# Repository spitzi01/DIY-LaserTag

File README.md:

# ESP32-LaserTag
Easy Open Source LaserTag System
### Überblick
Ziel dieses Projektes war der Bau eines einfachen LaserTag-Systems. Es sollte schnell und mit wenig Hardware an beliebigen Orten aufbaubar sein und  und über ein Handy gesteuert werden können.

Weitere Features sind:

- Soundausgabe für Schuss, Treffer und Nachladen (insgesamt 5 Verschiedene)
- Display in jedem Tagger
- lange Akkulaufzeit des gesamten Systems
- 3 Spielmodi
- Taschenlampe
- rote Laserdiode für Schuss-Simulation
- 5 in den Tagger integriete Infrarot-Empfänger
    
Das LaserTag-System besteht aus zwei elementaren Bestandteilen. Die Basisstation dient als Verbindungsglied zwischen den Taggern, der einzelnen Spieler, und einer HTTP-Website, welche der Konfiguration und Auswertung dient. Der Datenaustausch mit den Spielern erfolgt drahtlos mit Hilfe des EspNow-Protokolls der ESP32 S2 Mikrocontroller. Zum Spielen sind zwischen 2 und 10 Tagger notwendig. Für den Capture the Flag Spielmodus werden zusätzlich noch Flags benötigt, die die Basis und Spawnpunkt eines Team markieren.

### Basisstation

Nach dem Einschalten der Basisstation wird ein WLAN-Netzwerk erzeugt und die Konfigurationswebsite gehostet. Wenn man sich hier mit einem Smartphone einloggt, kann man die Anzahl der Spieler, Dauer des Spiels, Modus, Namen der Spieler und Teamzugehörigkeit einstellen. Die maximal 10 Spieler können auf 6 Teams verteilt werden. Vor dem Starten des Spiels mit dem Start-Taster müssen unbedingt alle Tagger, die verwendet werden sollen, eingeschaltet werden, damit diese von der Basisstation ihre Informationen erhalten können. Nach Ablauf der Spieldauer übermitteln die Tagger automatisch die Spielstände an die Basisstation und schalten sich ab. Die Basisstation berechnet die Ergebnisse und hostet diese in Form einer Website. Das hat den Vorteil, dass sich theoretisch mehrere Spieler die Ergebnisse auf ihren Smartphones anschauen können.

### Tagger

Bei einem Testsystem wurde festgestellt, dass es dem Spieler nicht möglich sein darf, seinen Tagger aus Versehen auszuschalten. Deshalb wird die Schaltung durch einen Taster aktiviert und nur durch den Mikrocontroller wieder deaktiviert. Außerdem soll der Spieler immer beide Hände am Tagger haben. So soll verhindert werden, dass man mit einer Hand Sensoren abdecken könnte. Dies wird durch einen Taster in Reihe zum eigentlichen Abzug realisiert. Gleichzeitig schaltet dieser auch die Taschenlampe an. In meinem Fall dient ein kleiner 12V Bleiakku aus einer Brandmeldezentrale als Energieversorgung. Mit Hilfe des Step Down Converters wird eine hohe Effizienz und Akkulaufzeit erreicht. Das Display hat 20 alphanumerische Stellen, welche die Namen der Spieler und die Anzahl der Leben anzeigen. Eine Hintergrundbeleuchtung ist nicht vorhanden, da diese zu viel Strom benötigen würde. Deshalb dient die RGB-LED für die Teamzugehörigkeit als Beleuchtung. Edit: Mittlerweile wurde das Display durch ein OLED 0,96" Display getauscht, da das LCD Display nicht mehr verfügbar war. Ebenso wurde der Akku durch einen günstigen 12V Lithium-Ionen Akku ersetzt.

Der Schuss wird durch eine Laserdiode visualisiert. Die eigentliche Information findet durch eine IR-Übertragung ihren Weg zu anderen Spielern. Bei Tests in der Nacht konnte eine Reichweite von bis zu 60 Meter erzielt werden. Der kurze Alu-Lauf dient als Reflektor für die Infrarot-LED und auch als Kühlkörper, da bei aktiviertem Schnellfeuermodus die LED sehr belastet wird.

Die verfügbaren Spielmodi sind:

- Standard (Spielen in Teams oder Einzeln, Reaktivierung nach ca. 20 Sekunden)
- Battle Royal (Spielen in Teams oder Einzeln, Leben werden bei Treffer weniger, kein Treffer in gewisser Zeit fügt ein Leben hinzu, lange Reaktivierungszeit ca. 2 Minuten)
- Capture the Flag (2 Teams rot & blau, Flags markieren Basis oder Spawnpunkt des jeweiligen Teams, Reaktivierung nur im Bereich des eigenen Spawnpunkts, Punkte bei Aufenthalt in gegnerischen Basis)

### Flag
Ein Flag sendet in regelmäßigen Abständen einen Code der von den Taggern empfangen wird. Bereich, in dem das Signal empfangbar ist, beträgt in etwa 5-8 Meter im Radius. Diese Strecke ergibt sich durch den Einsatz von ESP32 S2 Mikrocontroller ohne integriete Antenne in den Taggern.

### Verbesserungsmöglichkeiten

- Reichweite bei starkem Sonnenschein eingeschränkt
- Mikrocontroller überträgt kurzes Störgeräusch über I2S nach Ende einer Soundausgabe (Software Problem)
- Skalierbarkeit (mehr als 10 Spieler)

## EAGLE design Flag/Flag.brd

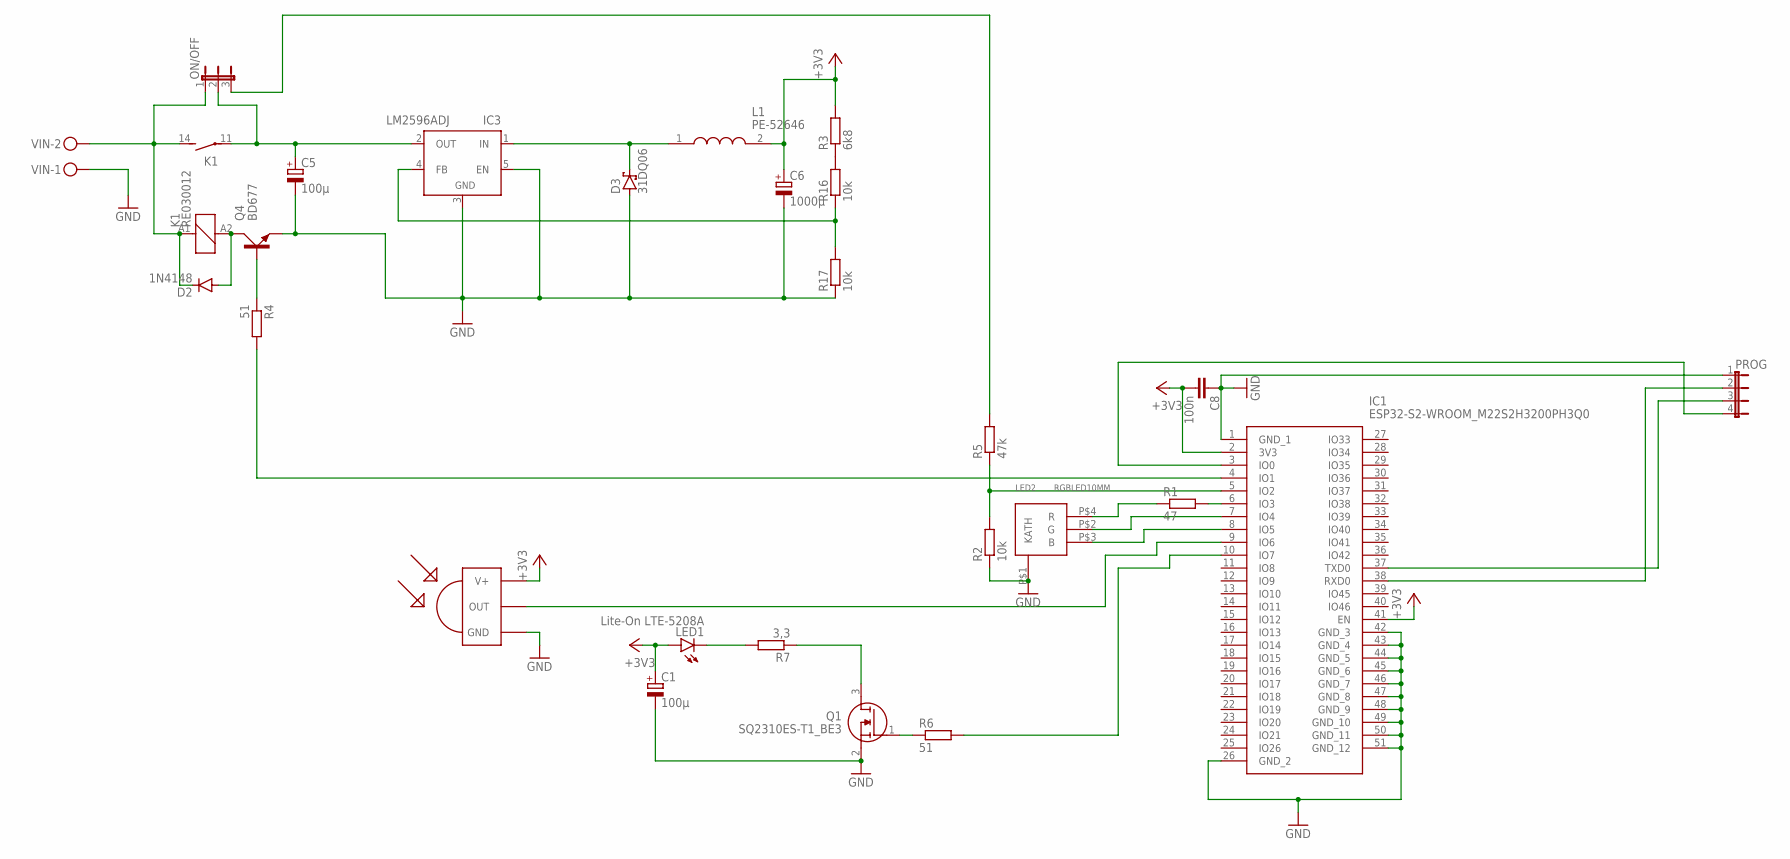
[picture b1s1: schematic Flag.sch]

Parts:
C1: 100µ; E3,5-8
C5: 100µ; E5-10,5
C6: 1000µ; E3,5-8
C8: 100n; C050-025X075
D2: 1N4148; SOD80C
D3: 31DQ06; C4111-15
IC1: ESP32-S2-WROOM_M22S2H3200PH3Q0; ESP32S2WROOMM22S2H3200PH3Q0
IC3: LM2596ADJ; TO220-52
K1: RE030012; RE-SCHRACK
L1: PE-52646; PE52646
LED1: Lite-On LTE-5208A; LED5MM
LED2: RGBLED10MM
ON/OFF: JP2E; JP2
PROG: JP4E; JP4
Q1: SQ2310ES-T1_BE3; SOT95P237X112-3N
Q4: BD677; TO126AV
R1: 47; 0207/10
R2: 10k; 0207/10
R3: 6k8; R1206
R4, R6: 51; R1206
R5: 47k; 0207/10
R7: 3,3; 0207/10
R16, R17: 10k; R1206
U1: TSOP33338; TSOP18XX
VIN: MKDSN1,5/2-5,08

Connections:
+3V3: C1.+, C6.+, C8.2, IC1.2 (3V3), IC1.41 (EN), L1.2, LED1.A, R3.2, U1.VCC (V+)
GND: C1.-, C5.-, C6.-, C8.1, D3.A, IC1.1 (GND_1), IC1.26 (GND_2), IC1.42 (GND_3), IC1.43 (GND_4), IC1.44 (GND_5), IC1.45 (GND_6), IC1.46 (GND_7), IC1.47 (GND_8), IC1.48 (GND_9), IC1.49 (GND_10), IC1.50 (GND_11), IC1.51 (GND_12), IC3.3 (GND), IC3.5 (EN), LED2.P$1 (KATH), PROG.1, Q1.2 (S), Q4.E, R2.1, R17.1, U1.GND, VIN.1
unnamed: C5.+, IC3.2 (OUT), K1.11, ON/OFF.2
unnamed: IC1.4 (IO1), R4.2
unnamed: D2.C, K1.14 (S), K1.A1 (1), ON/OFF.1, VIN.2
unnamed: D2.A, K1.A2 (2), Q4.C
unnamed: LED2.P$4 (R), R1.1
unnamed: IC1.7 (IO4), LED2.P$2 (G)
unnamed: IC1.8 (IO5), LED2.P$3 (B)
unnamed: D3.C, IC3.1 (IN), L1.1
unnamed: IC3.4 (FB), R16.1, R17.2
unnamed: IC1.6 (IO3), R1.2
unnamed: IC1.5 (IO2), R2.2, R5.1
unnamed: IC1.9 (IO6), U1.OUT
unnamed: ON/OFF.3, R5.2
unnamed: IC1.10 (IO7), R6.2
unnamed: Q1.1 (G), R6.1
unnamed: LED1.K (C), R7.2
unnamed: Q1.3 (D), R7.1
unnamed: Q4.B, R4.1
unnamed: IC1.3 (IO0), PROG.4
unnamed: IC1.37 (TXD0), PROG.3
unnamed: IC1.38 (RXD0), PROG.2
unnamed: R3.1, R16.2

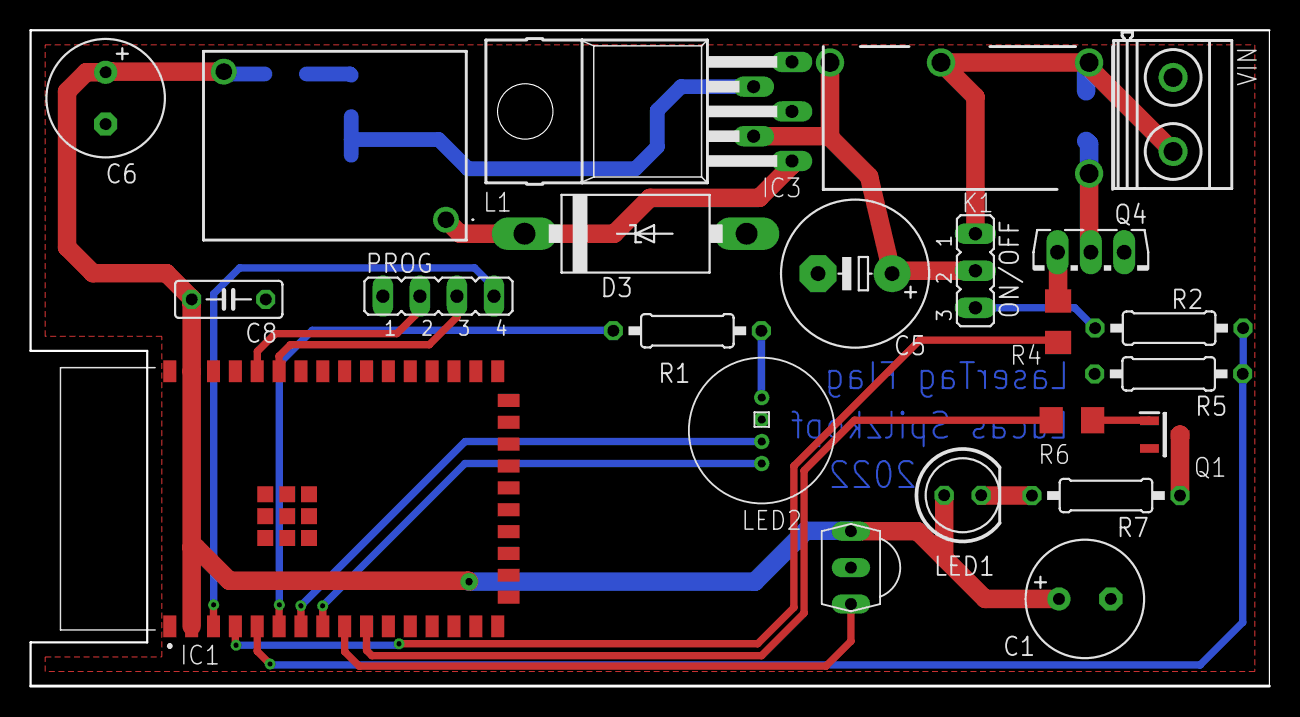
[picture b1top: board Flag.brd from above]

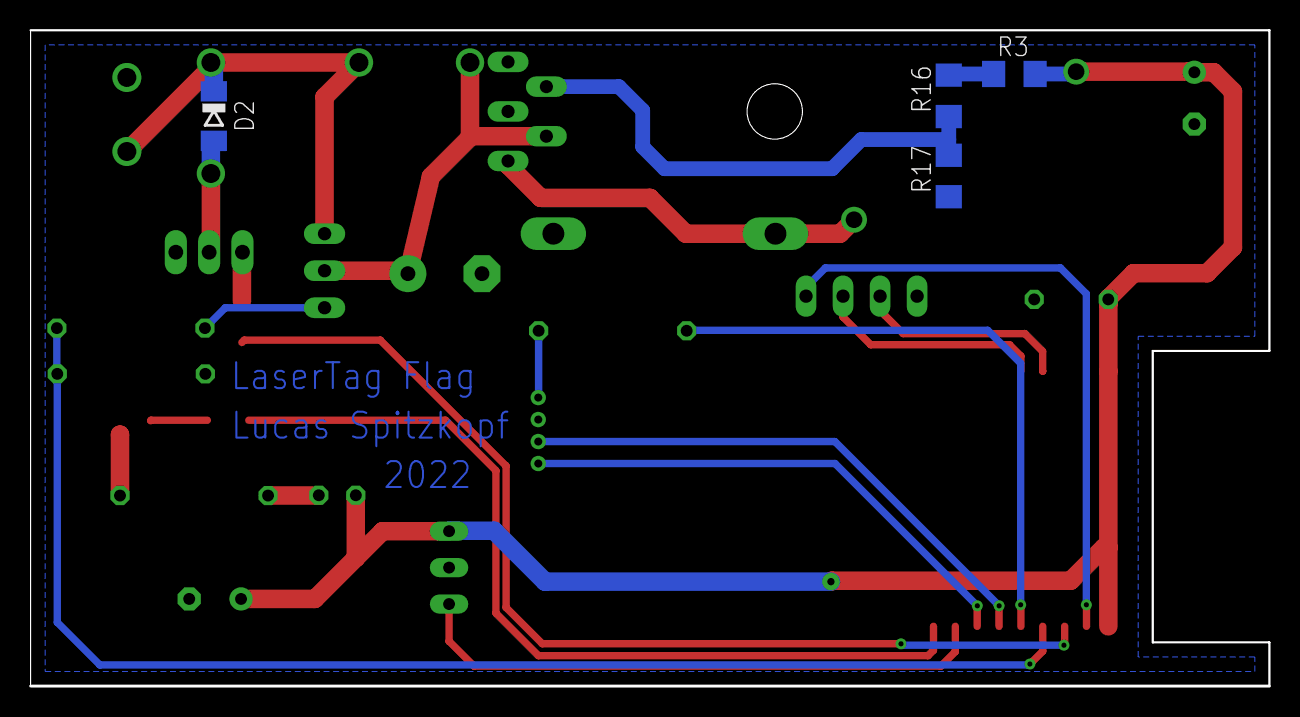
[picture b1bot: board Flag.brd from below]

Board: 2 copper layers, 85.0 x 45.0 mm, 27 parts (4 on the bottom side), 24 nets.

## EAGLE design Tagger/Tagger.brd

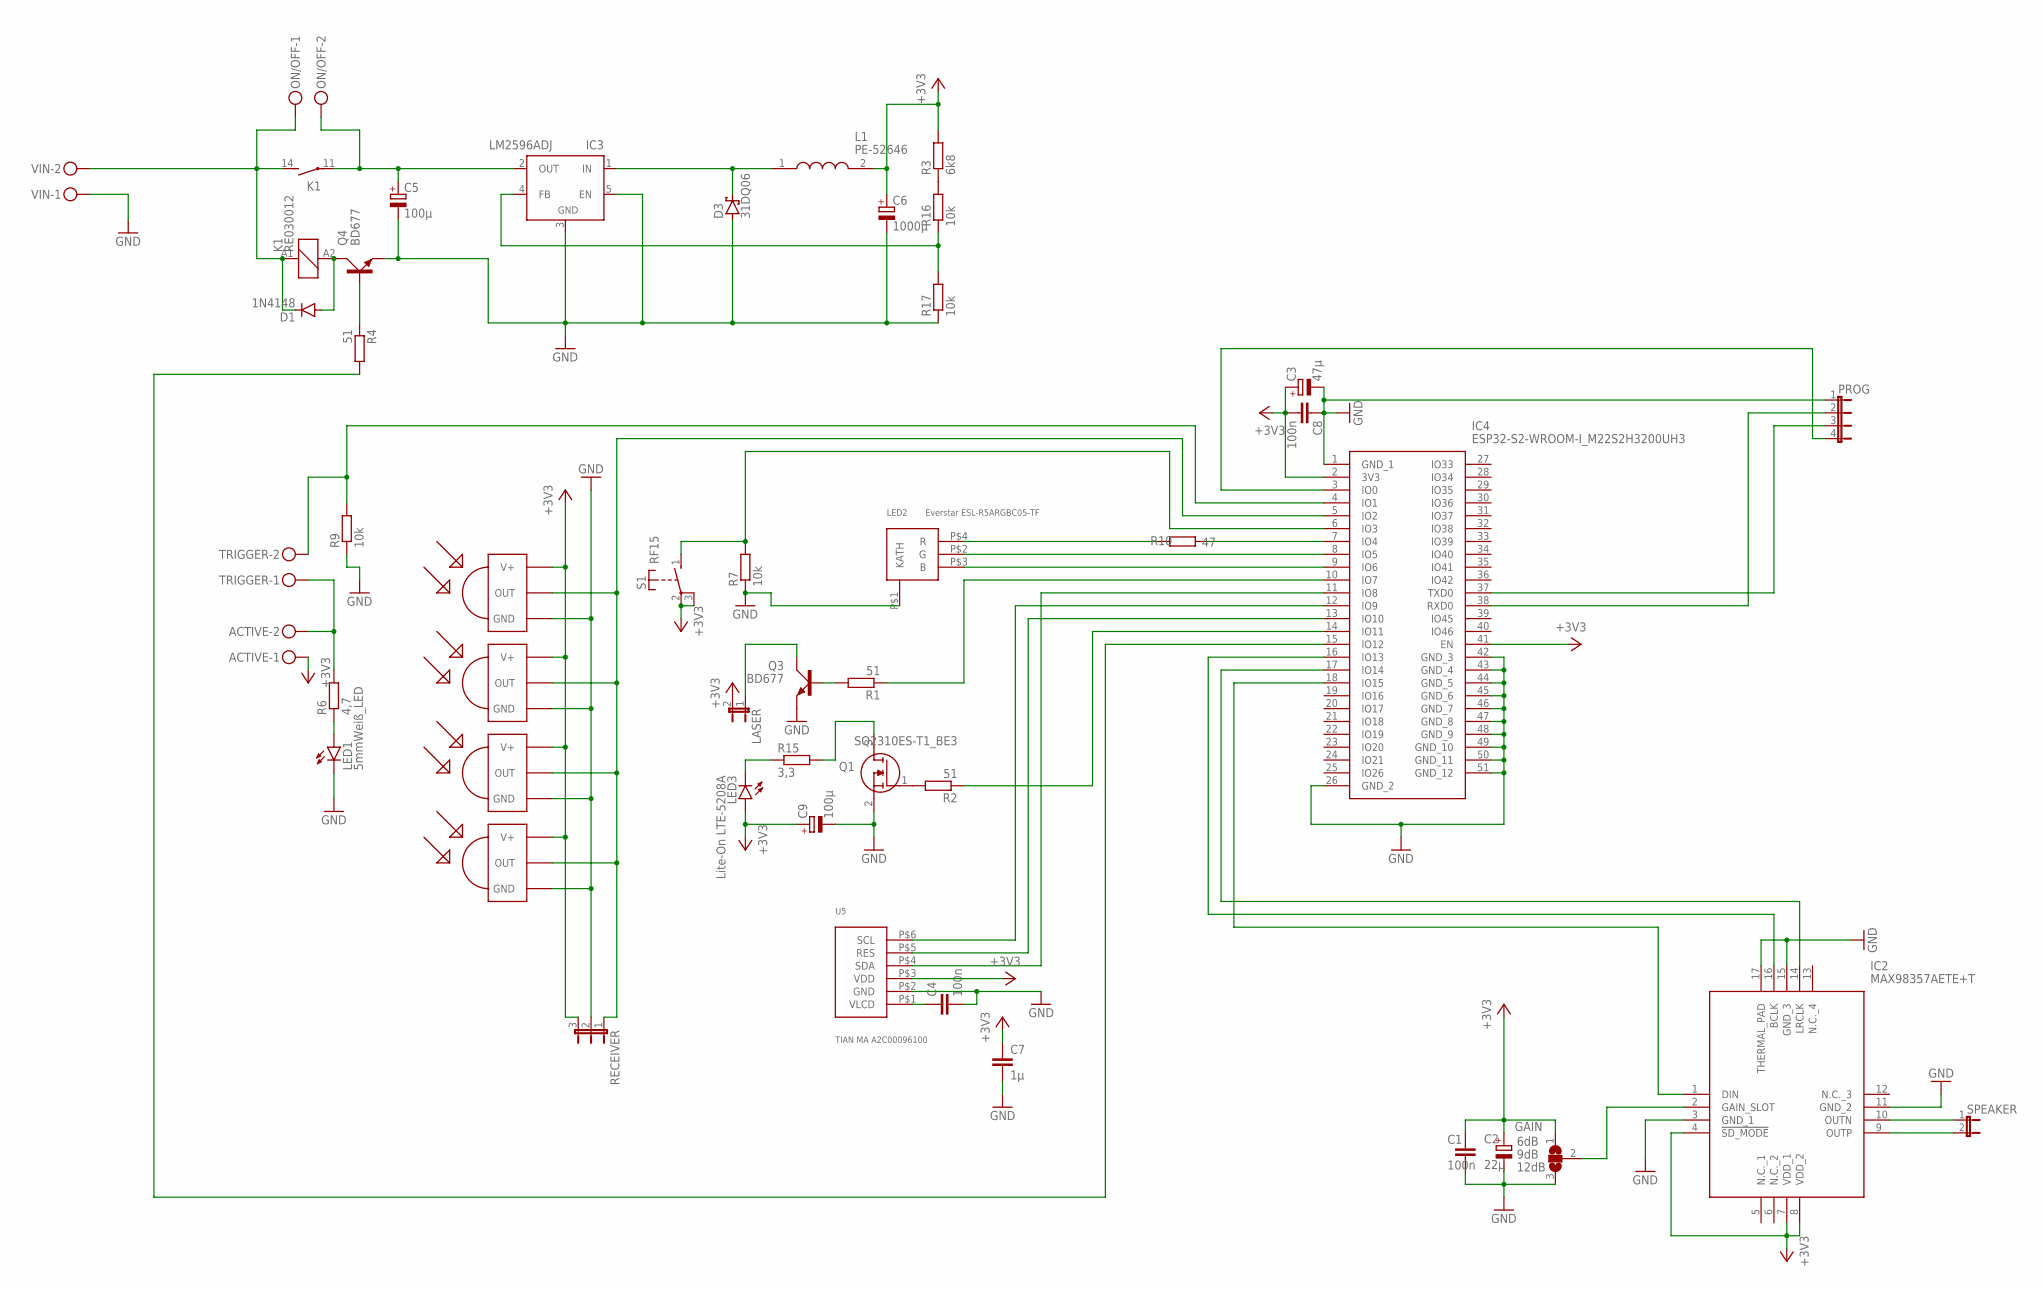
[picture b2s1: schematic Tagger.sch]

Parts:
ACTIVE: MKDSN1,5/2-5,08
C1, C4, C8: 100n; C1206
C2: 22µ; E2-5
C3: 47µ; E2-5
C5: 100µ; E2,5-6E
C6: 1000µ; E5-10,5
C7: 1µ; C0805
C9: 100µ; E2,5-6
D1: 1N4148; SOD80C
D3: 31DQ06; C4111-15
GAIN: SJ2WW; SJ_2W
IC2: MAX98357AETE+T; QFN50P300X300X80-17N
IC3: LM2596ADJ; TO220-52
IC4: ESP32-S2-WROOM-I_M22S2H3200UH3; ESP32S2WROOMIM22S2H3200UH3Q0
K1: RE030012; RE-SCHRACK
L1: PE-52646; PE52646
LASER: JP1E; JP1
LED1: 5mmWeiß_LED; LED5MM
LED2: Everstar ESL-R5ARGBC05-TF; RGBLED5MM
LED3: Lite-On LTE-5208A; LED5MM
ON/OFF: MKDSN1,5/2-5,08
PROG: JP4E; JP4
Q1: SQ2310ES-T1_BE3; SOT95P237X112-3N
Q3, Q4: BD677; TO126AV
R1, R2, R4: 51; R1206
R3: 6k8; R1206
R6: 4,7; 0207/10
R7, R9, R16, R17: 10k; R1206
R10: 47; 0207/10
R15: 3,3; 0207/10
RECEIVER: JP2E; JP2
S1: RF15
SPEAKER: JP1E; JP1
TRIGGER: MKDSN1,5/2-5,08
U1, U2, U3, U4: TSOP33338; TSOP18XX
U5: TIAN MA A2C00096100; LCD_DISPLAY
VIN: MKDSN1,5/2-5,08

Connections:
+3V3: ACTIVE.1, C1.1, C2.+, C3.+, C6.+, C7.1, C8.2, C9.+, GAIN.1, IC2.4 (!SD_MODE), IC2.7 (VDD_1), IC2.8 (VDD_2), IC4.2 (3V3), IC4.41 (EN), L1.2, LASER.2, LED3.A, R3.2, RECEIVER.3, S1.2, S1.3, U1.VCC (V+), U2.VCC (V+), U3.VCC (V+), U4.VCC (V+), U5.P$3 (VDD)
GND: C1.2, C2.-, C3.-, C4.2, C5.-, C6.-, C7.2, C8.1, C9.-, D3.A, GAIN.3, IC2.3 (GND_1), IC2.11 (GND_2), IC2.15 (GND_3), IC2.17 (THERMAL_PAD), IC3.3 (GND), IC3.5 (EN), IC4.1 (GND_1), IC4.26 (GND_2), IC4.42 (GND_3), IC4.43 (GND_4), IC4.44 (GND_5), IC4.45 (GND_6), IC4.46 (GND_7), IC4.47 (GND_8), IC4.48 (GND_9), IC4.49 (GND_10), IC4.50 (GND_11), IC4.51 (GND_12), LED1.K (C), LED2.P$1 (KATH), PROG.1, Q1.2 (S), Q3.E, Q4.E, R7.1, R9.1, R17.1, RECEIVER.2, U1.GND, U2.GND, U3.GND, U4.GND, U5.P$2 (GND), VIN.1
unnamed: C5.+, IC3.2 (OUT), K1.11, ON/OFF.2
unnamed: GAIN.2, IC2.2 (GAIN_SLOT)
unnamed: D1.C, K1.14 (S), K1.A1 (1), ON/OFF.1, VIN.2
unnamed: D1.A, K1.A2 (2), Q4.C
unnamed: IC4.7 (IO4), R10.2
unnamed: IC2.10 (OUTN), SPEAKER.1
unnamed: IC2.1 (DIN), IC4.18 (IO15)
unnamed: C4.1, U5.P$1 (VLCD)
unnamed: D3.C, IC3.1 (IN), L1.1
unnamed: IC3.4 (FB), R16.1, R17.2
unnamed: IC2.14 (LRCLK), IC4.17 (IO14)
unnamed: IC4.14 (IO11), R2.1
unnamed: LED3.K (C), R15.1
unnamed: LASER.1, Q3.C
unnamed: LED1.A, R6.1
unnamed: IC4.11 (IO8), U5.P$4 (SDA)
unnamed: Q1.3 (D), R15.2
unnamed: IC4.6 (IO3), R7.2, S1.1 (S)
unnamed: Q4.B, R4.1
unnamed: LED2.P$4 (R), R10.1
unnamed: IC4.8 (IO5), LED2.P$2 (G)
unnamed: IC4.9 (IO6), LED2.P$3 (B)
unnamed: IC2.16 (BCLK), IC4.16 (IO13)
unnamed: IC4.4 (IO1), R9.2, TRIGGER.2
unnamed: IC4.10 (IO7), R1.1
unnamed: Q3.B, R1.2
unnamed: IC4.13 (IO10), U5.P$5 (RES)
unnamed: IC4.12 (IO9), U5.P$6 (SCL)
unnamed: IC2.9 (OUTP), SPEAKER.2
unnamed: IC4.3 (IO0), PROG.4
unnamed: Q1.1 (G), R2.2
unnamed: IC4.5 (IO2), RECEIVER.1, U1.OUT, U2.OUT, U3.OUT, U4.OUT
unnamed: IC4.37 (TXD0), PROG.3
unnamed: IC4.38 (RXD0), PROG.2
unnamed: ACTIVE.2, R6.2, TRIGGER.1
unnamed: R3.1, R16.2
unnamed: IC4.15 (IO12), R4.2

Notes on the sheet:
12dB
9dB
6dB

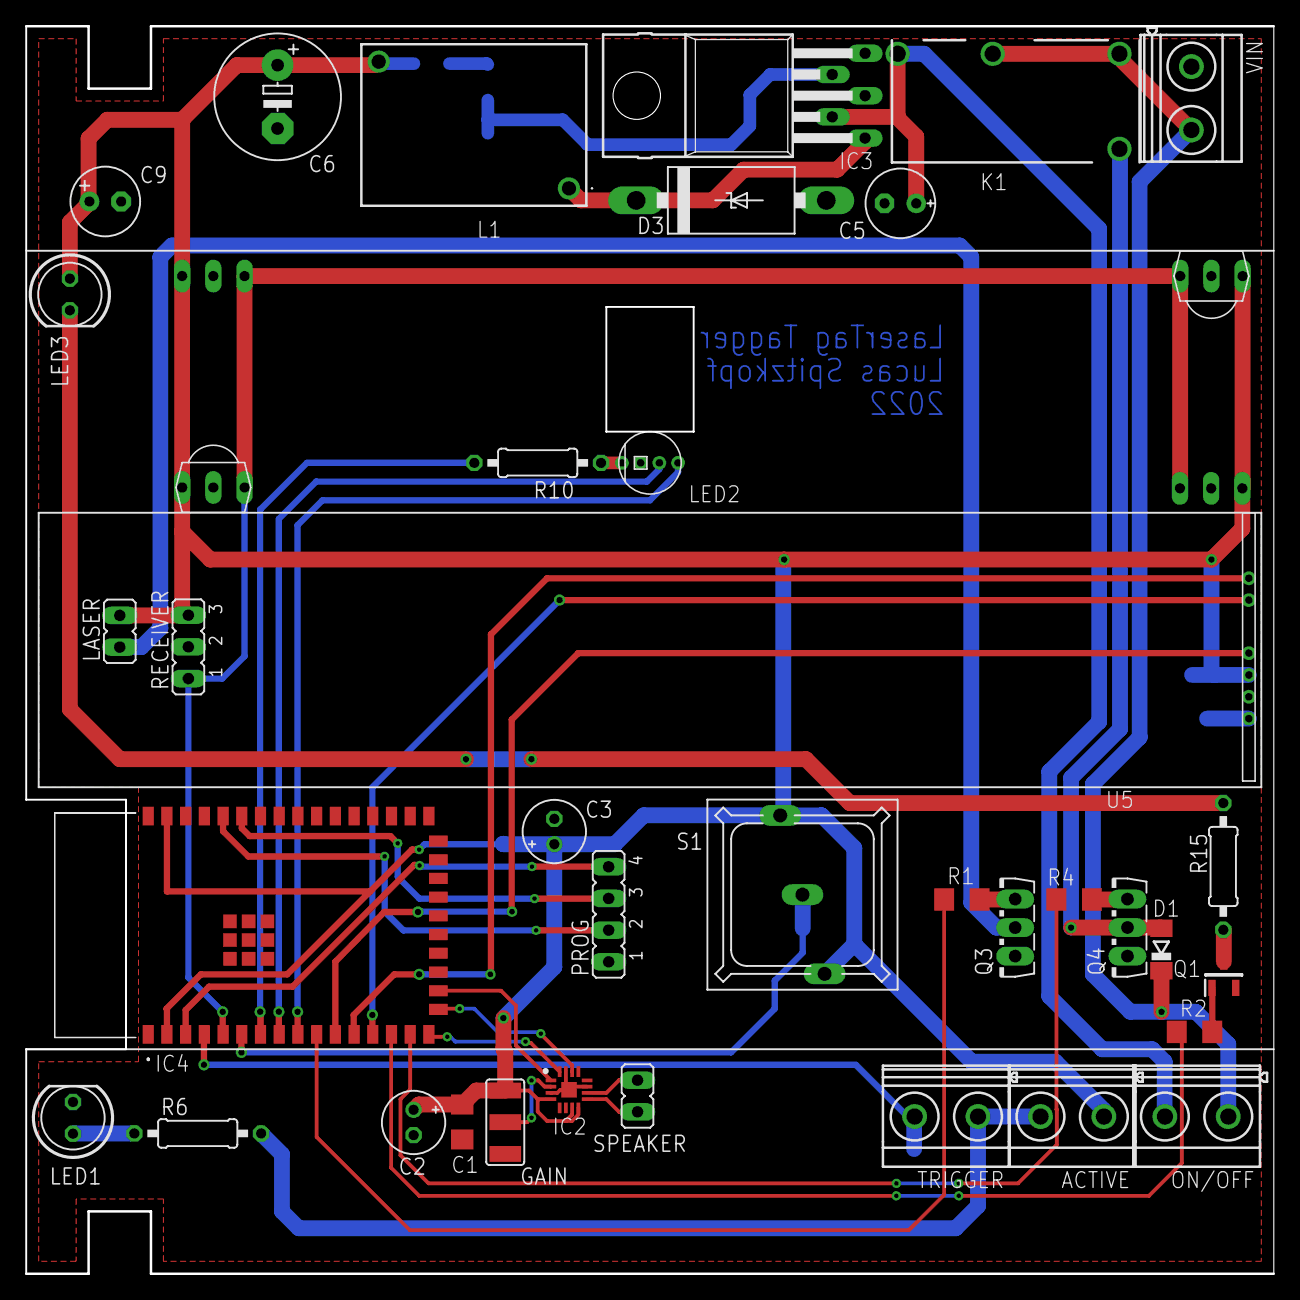
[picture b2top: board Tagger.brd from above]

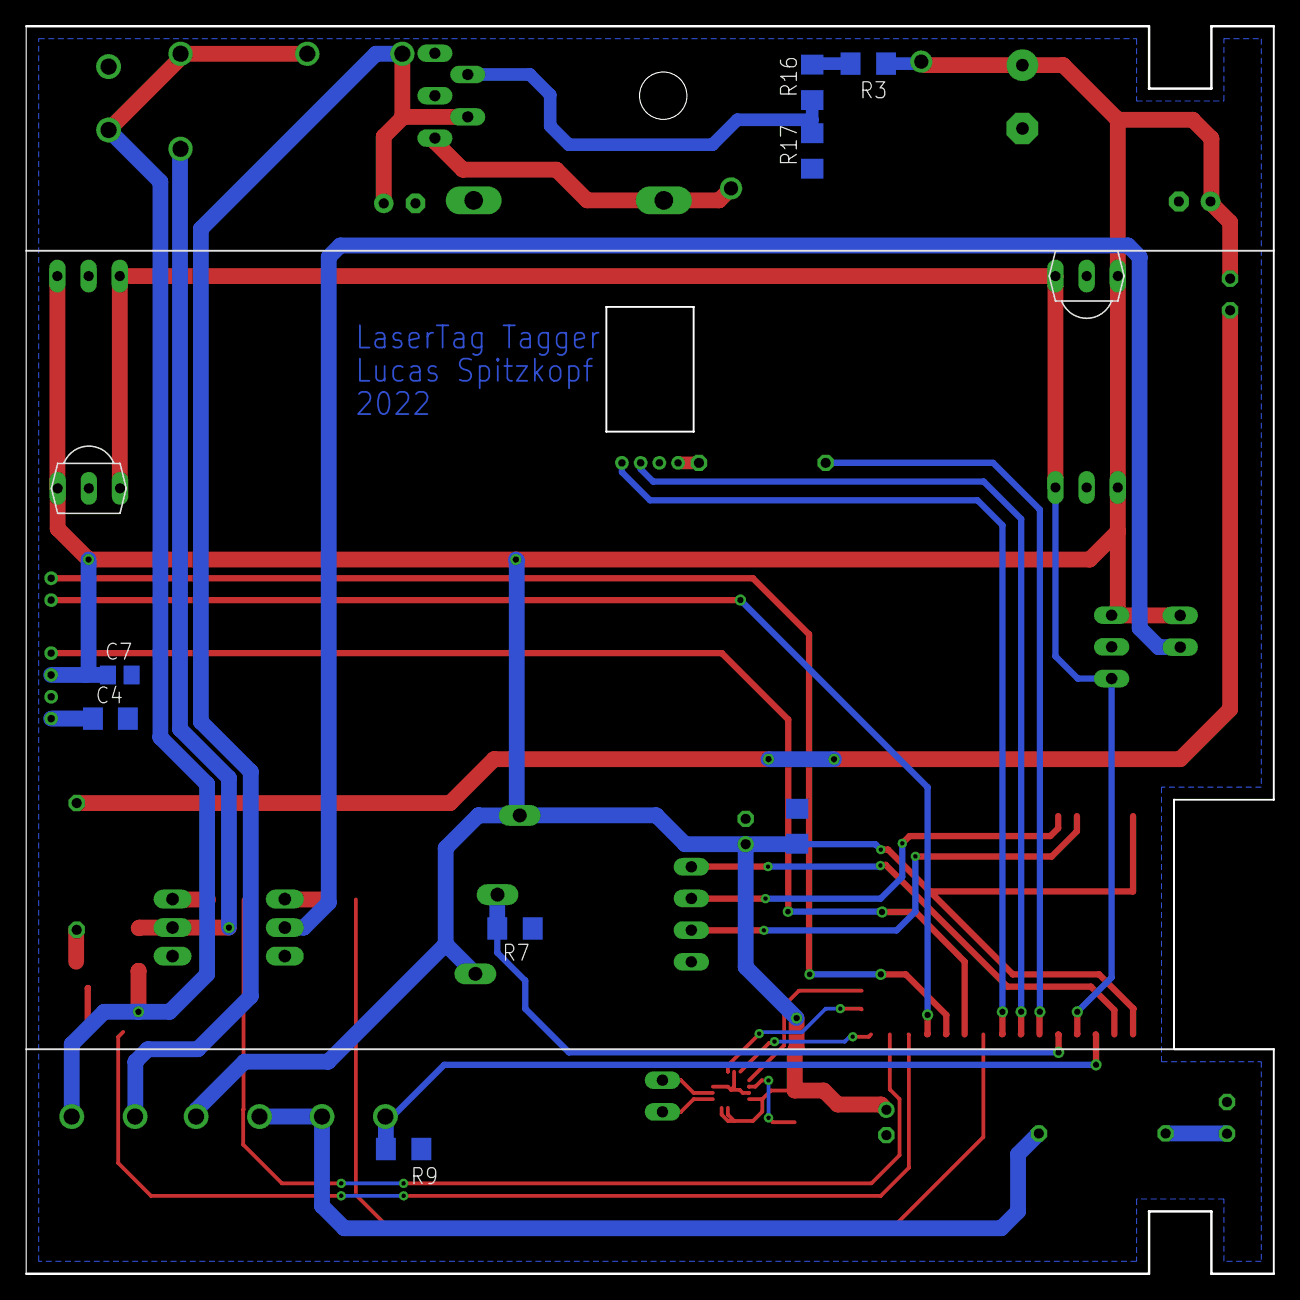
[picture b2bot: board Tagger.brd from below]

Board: 2 copper layers, 100.0 x 100.0 mm, 48 parts (10 on the bottom side), 39 nets.

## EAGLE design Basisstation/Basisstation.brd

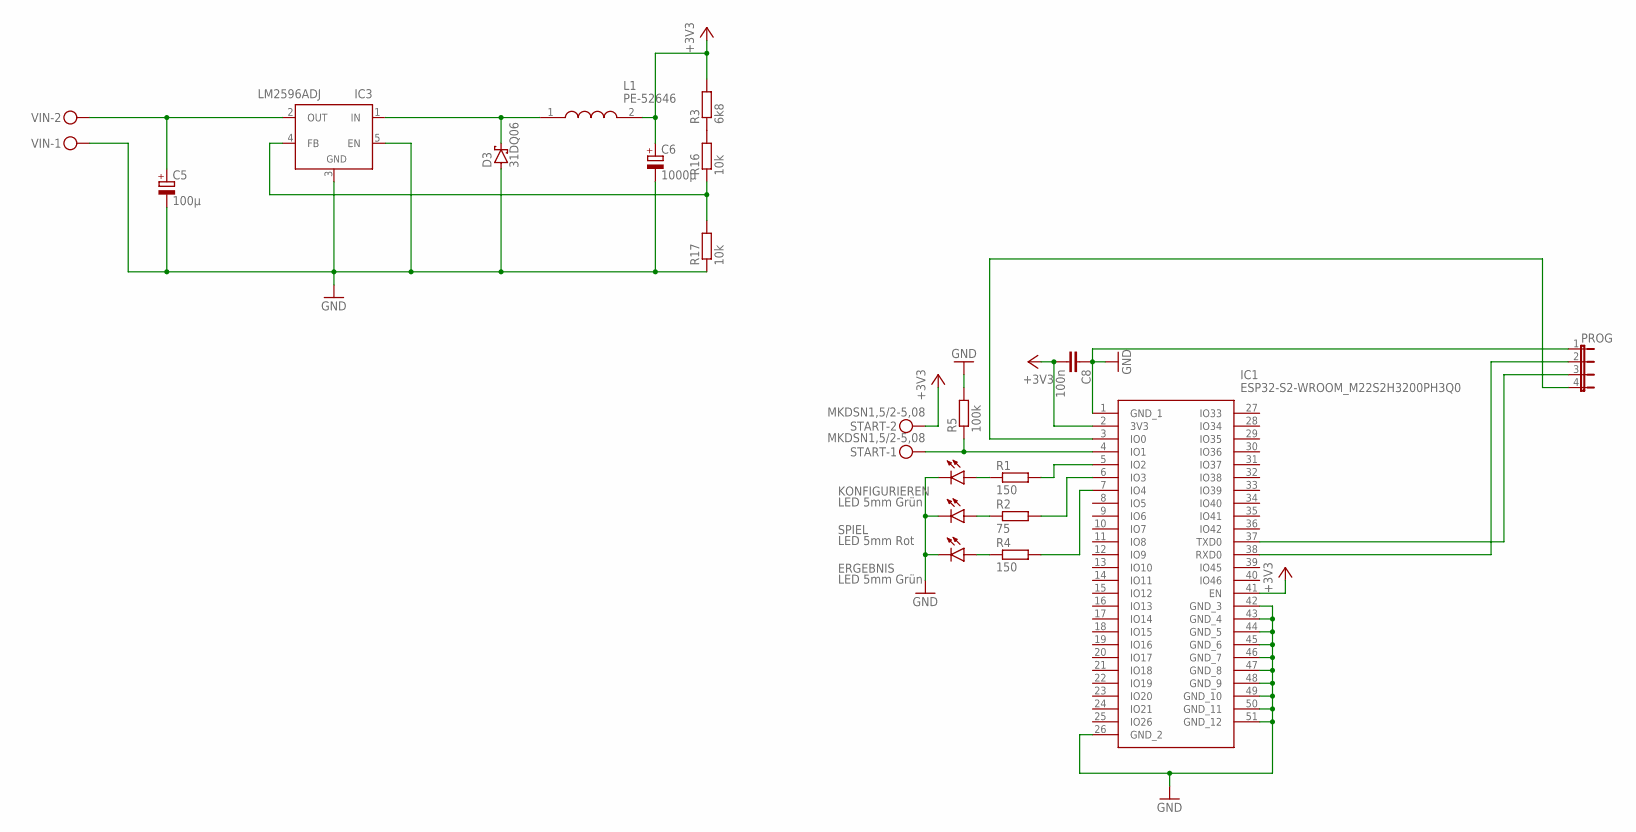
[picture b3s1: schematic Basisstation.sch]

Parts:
C5: 100µ; E5-10,5
C6: 1000µ; E3,5-8
C8: 100n; C050-025X075
D3: 31DQ06; C4111-15
ERGEBNIS: LED 5mm Grün; LED5MM
IC1: ESP32-S2-WROOM_M22S2H3200PH3Q0; ESP32S2WROOMM22S2H3200PH3Q0
IC3: LM2596ADJ; TO220-52
KONFIGURIEREN: LED 5mm Grün; LED5MM
L1: PE-52646; PE52646
PROG: JP4E; JP4
R1, R4: 150; 0207/10
R2: 75; 0207/10
R3: 6k8; R1206
R5: 100k; 0207/10
R16, R17: 10k; R1206
SPIEL: LED 5mm Rot; LED5MM
START: MKDSN1,5/2-5,08
VIN: MKDSN1,5/2-5,08

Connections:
+3V3: C6.+, C8.2, IC1.2 (3V3), IC1.41 (EN), L1.2, R3.2, START.2
GND: C5.-, C6.-, C8.1, D3.A, ERGEBNIS.K (C), IC1.1 (GND_1), IC1.26 (GND_2), IC1.42 (GND_3), IC1.43 (GND_4), IC1.44 (GND_5), IC1.45 (GND_6), IC1.46 (GND_7), IC1.47 (GND_8), IC1.48 (GND_9), IC1.49 (GND_10), IC1.50 (GND_11), IC1.51 (GND_12), IC3.3 (GND), IC3.5 (EN), KONFIGURIEREN.K (C), PROG.1, R5.2, R17.1, SPIEL.K (C), VIN.1
unnamed: IC1.5 (IO2), R1.2
unnamed: IC1.4 (IO1), R5.1, START.1
unnamed: C5.+, IC3.2 (OUT), VIN.2
unnamed: KONFIGURIEREN.A, R1.1
unnamed: R2.1, SPIEL.A
unnamed: ERGEBNIS.A, R4.1
unnamed: IC1.6 (IO3), R2.2
unnamed: IC1.7 (IO4), R4.2
unnamed: D3.C, IC3.1 (IN), L1.1
unnamed: IC3.4 (FB), R16.1, R17.2
unnamed: IC1.3 (IO0), PROG.4
unnamed: IC1.37 (TXD0), PROG.3
unnamed: IC1.38 (RXD0), PROG.2
unnamed: R3.1, R16.2

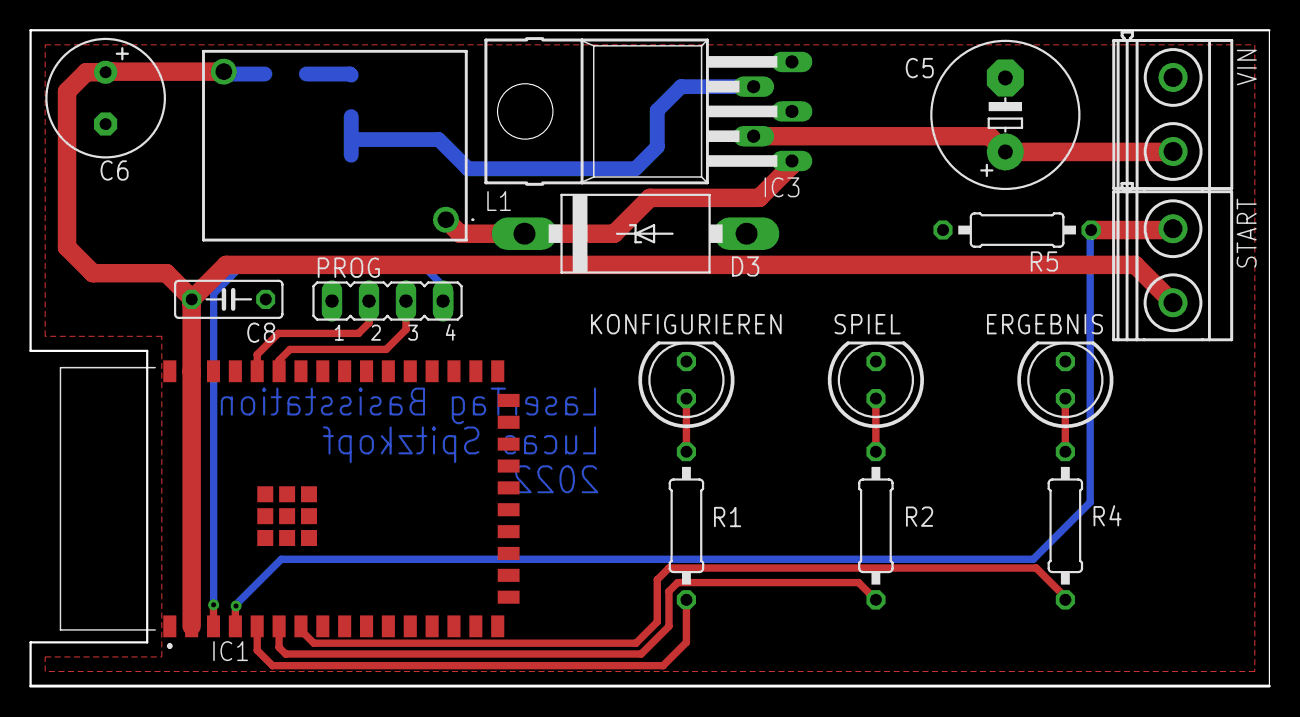
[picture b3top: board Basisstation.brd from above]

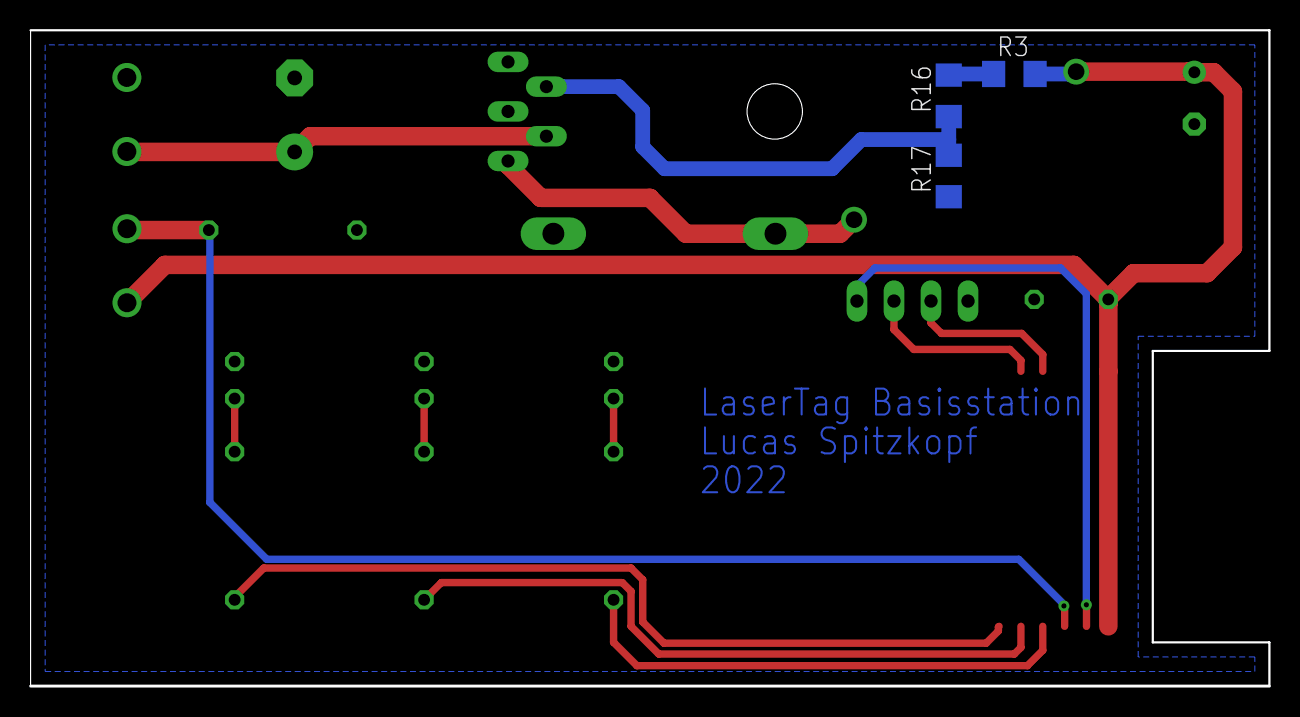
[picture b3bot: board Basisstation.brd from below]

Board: 2 copper layers, 85.0 x 45.0 mm, 20 parts (3 on the bottom side), 16 nets.

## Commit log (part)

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2022-03-29 Create LICENSE
2022-09-05 Rename LaserTag1.ino to Tagger1.ino
2022-09-05 Rename LaserTag2.ino to Tagger2.ino
2022-09-05 Rename LaserTag10.ino to Tagger10.ino
2022-09-05 Rename LaserTag3.ino to Tagger3.ino
2022-09-05 Rename LaserTag4.ino to Tagger4.ino
2022-09-05 Rename LaserTag5.ino to Tagger5.ino
2022-09-05 Rename LaserTag6.ino to Tagger6.ino
2022-09-05 Rename LaserTag7.ino to Tagger7.ino
2022-09-05 Rename LaserTag8.ino to Tagger8.ino
2022-09-05 Rename LaserTag9.ino to Tagger9.ino
